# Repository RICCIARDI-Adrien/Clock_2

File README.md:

# Clock 2

Improved digital clock. First generation is [here](https://github.com/RICCIARDI-Adrien/Clock).  

New features :
* Improved temperature sensor.
* Humidity sensor.
* Pressure sensor.
* High accuracy temperature-compensated RTC.
* More compact, more industrial and more robust casing.
* A really simple interface made of 3 buttons to configure all clock settings (no more configuration through USB).

## Firmware

Microchip XC8 version 2.20 or above is required to build the firmware. Previous XC8 versions will work but the Celsius degree unit won't be displayed. This is due to a bug in XC8 escaped string characters parsing.

On a Linux system with XC8 installed and added to `PATH`, enter the following lines :
```
cd <repository directory>/Software
make
```

Resulting firmware file is `Firmware.hex`.

## Photo gallery

### PCB

### Display

### Casing

### Finished clock

Alarm stopping and display backlight button :

Power supply USB connector :

Bottom protection pads :

Internal view (backup battery not yet fitted) :

## Views

### Main

```
+--------------------+
|      11:16:23      |
|Jeudi    19/03/2020 |
| T:23°C  P:1112mBar |
| H:68%   A:OFF      |
+--------------------+
```

```
+--------------------+
|       0:37:11      |
|Dimanche 06/09/2020 |
| T:27°C  P:983mBar  |
| H:50%   A:ON(08:30)|
+--------------------+
```

'A' stands for a bell symbol representing the current alarm state (enabled or disabled).

### Statistics

Press `+` button to reach temperature view.  
Press `-` button to reach humidity view (these views can be accessed in reverse order).

```
+--------------------+
|---- TEMPERATURE ---|
|Minimum : 23°C      |
|Maximum : 15°C      |
|                    |
+--------------------+
```

Press `Set` or `-` button to return to main view.  
Press `+` button to go to pressure view.

```
+--------------------+
|----- PRESSION -----|
|Minimum : 980mbar   |
|Maximum : 1002mbar  |
|                    |
+--------------------+
```

Press `Set` to immediately return to main view.  
Press `-` button to return to temperature view.  
Press `+` button to go to humidity view.

```
+--------------------+
|----- HUMIDITE -----|
|Minimum : 57%       |
|Maximum : 59%       |
|                    |
+--------------------+
```

Press `Set` or `+` button to return to main view.  
Press `-` button to return to pression view.

### Settings

Press `Set` button to reach this view.

```
+--------------------+
|-> Régler alarme    |
|   Régler heure     |
|   Régler date      |
|       Retour       |
+--------------------+
```
Select a menu entry using `+` and `-` buttons, then press `Set` button.

### Set alarm

```
+--------------------+
|--- HEURE ALARME ---|
| Heure : 7          |
| + et - pour régler |
| SET pour continuer |
+--------------------+
```
Press `+` and `-` buttons to choose an hour, then press `Set` button to continue.

```
+--------------------+
|-- MINUTES ALARME --|
| Minutes : 30       |
| + et - pour régler |
| SET pour continuer |
+--------------------+
```
Press `+` and `-` buttons to choose minutes value, then press `Set` button to return to settings menu.

### Set time

```
+--------------------+
|--- REGLER HEURE ---|
| Heure : 11         |
| + et - pour régler |
| SET pour continuer |
+--------------------+
```
Press `+` and `-` buttons to choose an hour, then press `Set` button to continue.

```
+--------------------+
|-- REGLER MINUTES --|
| Minutes : 26       |
| + et - pour régler |
| SET pour continuer |
+--------------------+
```
Press `+` and `-` buttons to choose minutes value, then press `Set` button to continue.

```
+--------------------+
|- REGLER SECONDES --|
| Secondes : 47      |
| + et - pour régler |
| SET pour continuer |
+--------------------+
```
Press `+` and `-` buttons to choose seconds value, then press `Set` button to return to settings menu.

### Set date

```
+--------------------+
|--- REGLER JOUR ----|
| Jour : 14          |
| + et - pour régler |
| SET pour continuer |
+--------------------+
```
Press `+` and `-` buttons to choose a day, then press `Set` button to continue.

```
+--------------------+
|--- REGLER MOIS ----|
| Mois : 3           |
| + et - pour régler |
| SET pour continuer |
+--------------------+
```
Press `+` and `-` buttons to choose a month, then press `Set` button to continue.

```
+--------------------+
|--- REGLER ANNEE ---|
| Année : 2020       |
| + et - pour régler |
| SET pour continuer |
+--------------------+
```
Press `+` and `-` buttons to choose a year, then press `Set` button to return to settings menu.

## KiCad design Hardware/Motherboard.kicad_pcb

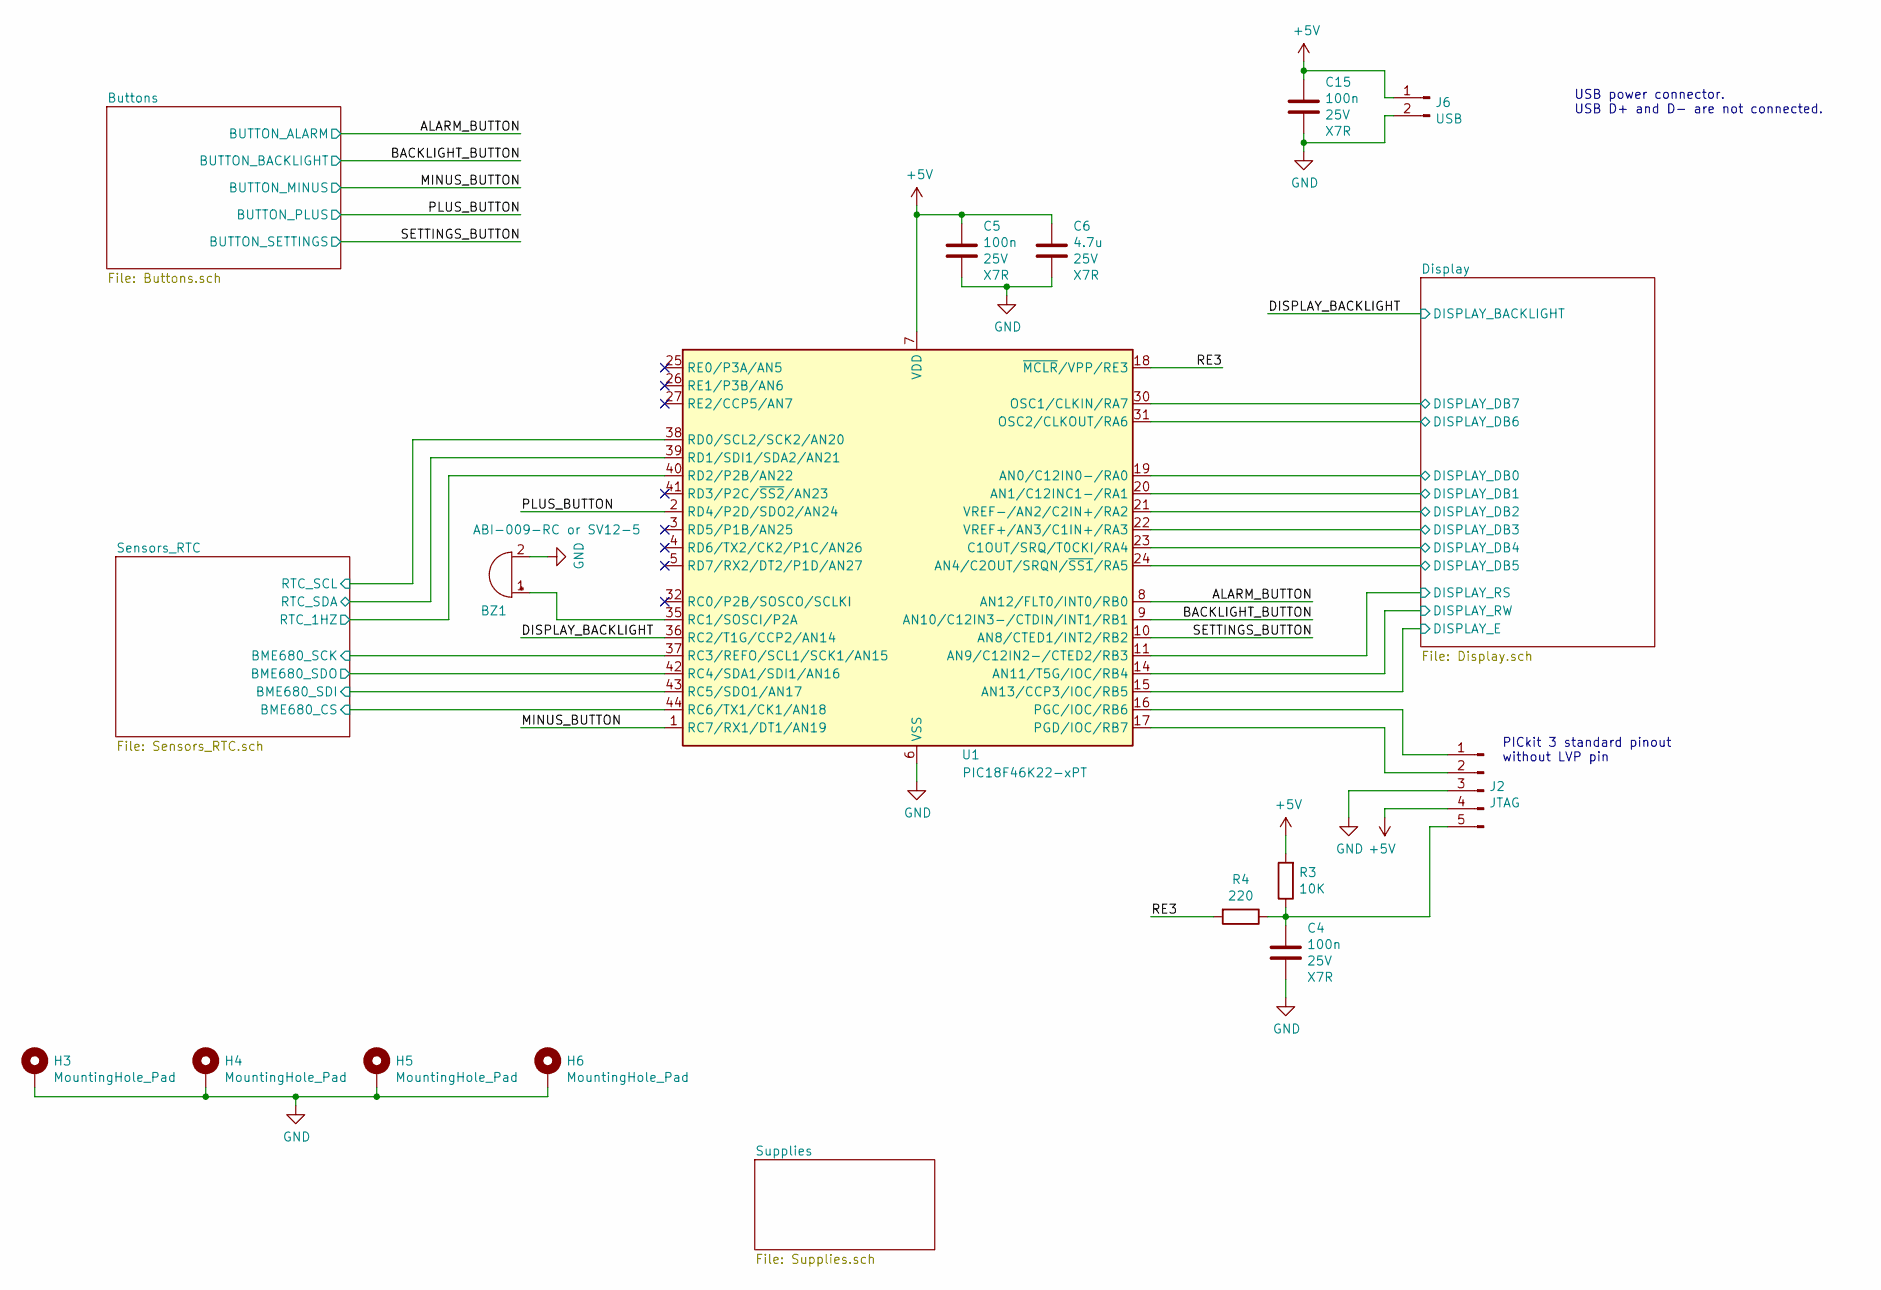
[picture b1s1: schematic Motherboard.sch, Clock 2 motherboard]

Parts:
BZ1: ABI-009-RC or SV12-5; MagneticBuzzer_ProSignal_ABI-009-RC
C4, C5, C15: 100n; C_1206_3216Metric_Pad1.42x1.75mm_HandSolder
C6: 4.7u; C_1206_3216Metric_Pad1.42x1.75mm_HandSolder
H3, H4, H5, H6: MountingHole_Pad; MountingHole_4.5mm_Pad
J2: JTAG; PinHeader_1x05_P2.54mm_Horizontal
J6: USB; PinHeader_1x02_P2.54mm_Vertical
R3: 10K; R_1206_3216Metric_Pad1.42x1.75mm_HandSolder
R4: 220; R_1206_3216Metric_Pad1.42x1.75mm_HandSolder
U1: PIC18F46K22-xPT; TQFP-44_10x10mm_P0.8mm

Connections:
+5V: C5.1, C6.1, C15.1, J2.4, J6.1, R3.2, U1.7 (VDD), U1.28 (VDD); also elsewhere on the board
/ALARM_BUTTON: U1.8 (AN12/FLT0/INT0/RB0); also elsewhere on the board
/BACKLIGHT_BUTTON: U1.9 (AN10/C12IN3-/CTDIN/INT1/RB1); also elsewhere on the board
/DISPLAY_BACKLIGHT: U1.36 (RC2/T1G/CCP2/AN14); also elsewhere on the board
/Display/DISPLAY_DB0: U1.19 (AN0/C12IN0-/RA0); also elsewhere on the board
/Display/DISPLAY_DB1: U1.20 (AN1/C12INC1-/RA1); also elsewhere on the board
/Display/DISPLAY_DB2: U1.21 (VREF-/AN2/C2IN+/RA2); also elsewhere on the board
/Display/DISPLAY_DB3: U1.22 (VREF+/AN3/C1IN+/RA3); also elsewhere on the board
/Display/DISPLAY_DB4: U1.23 (C1OUT/SRQ/T0CKI/RA4); also elsewhere on the board
/Display/DISPLAY_DB5: U1.24 (AN4/C2OUT/SRQN/~SS1~/RA5); also elsewhere on the board
/Display/DISPLAY_DB6: U1.31 (OSC2/CLKOUT/RA6); also elsewhere on the board
/Display/DISPLAY_DB7: U1.30 (OSC1/CLKIN/RA7); also elsewhere on the board
/Display/DISPLAY_E: U1.15 (AN13/CCP3/IOC/RB5); also elsewhere on the board
/Display/DISPLAY_RS: U1.11 (AN9/C12IN2-/CTED2/RB3); also elsewhere on the board
/Display/DISPLAY_RW: U1.14 (AN11/T5G/IOC/RB4); also elsewhere on the board
/MINUS_BUTTON: U1.1 (RC7/RX1/DT1/AN19); also elsewhere on the board
/PLUS_BUTTON: U1.2 (RD4/P2D/SDO2/AN24); also elsewhere on the board
/RE3: R4.2, U1.18 (~MCLR~/VPP/RE3)
/SETTINGS_BUTTON: U1.10 (AN8/CTED1/INT2/RB2); also elsewhere on the board
/Sensors_RTC/BME680_CS: U1.44 (RC6/TX1/CK1/AN18); also elsewhere on the board
/Sensors_RTC/BME680_SCK: U1.37 (RC3/REFO/SCL1/SCK1/AN15); also elsewhere on the board
/Sensors_RTC/BME680_SDI: U1.43 (RC5/SDO1/AN17); also elsewhere on the board
/Sensors_RTC/BME680_SDO: U1.42 (RC4/SDA1/SDI1/AN16); also elsewhere on the board
/Sensors_RTC/RTC_1HZ: U1.40 (RD2/P2B/AN22); also elsewhere on the board
/Sensors_RTC/RTC_SCL: U1.38 (RD0/SCL2/SCK2/AN20); also elsewhere on the board
/Sensors_RTC/RTC_SDA: U1.39 (RD1/SDI1/SDA2/AN21); also elsewhere on the board
GND: BZ1.2 (+), C4.2, C5.2, C6.2, C15.2, H3.1, H4.1, H5.1, H6.1, J2.3, J6.2, U1.6 (VSS), U1.29 (VSS); also elsewhere on the board
unnamed: BZ1.1 (-), U1.35 (RC1/SOSCI/P2A)
unnamed: C4.1, J2.5, R3.1, R4.1
unnamed: J2.1, U1.16 (PGC/IOC/RB6)
unnamed: J2.2, U1.17 (PGD/IOC/RB7)

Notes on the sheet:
PICkit 3 standard pinout without LVP pin
USB power connector. USB D+ and D- are not connected.

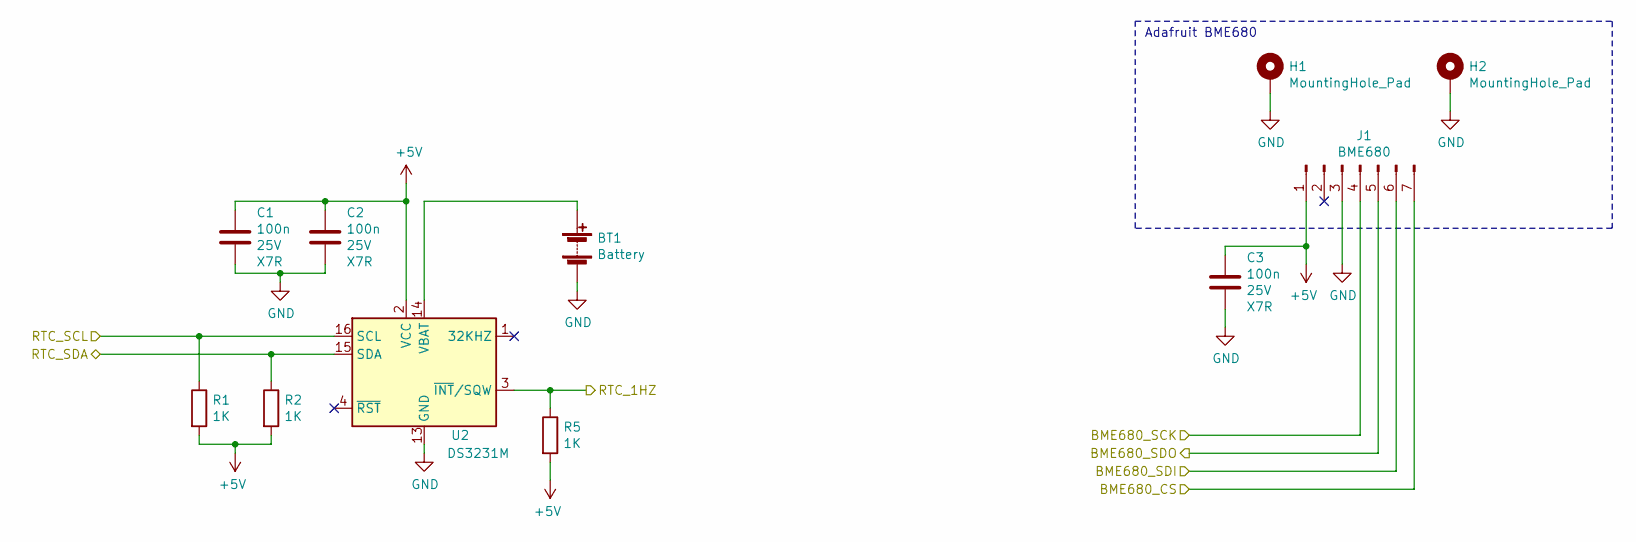
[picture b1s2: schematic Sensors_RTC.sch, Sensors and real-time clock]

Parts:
BT1: Battery; BatteryHolder_Keystone_103_1x20mm
C1, C2, C3: 100n; C_1206_3216Metric_Pad1.42x1.75mm_HandSolder
H1, H2: MountingHole_Pad; MountingHole_2.7mm_Pad
J1: BME680; PinHeader_1x07_P2.54mm_Vertical
R1, R2, R5: 1K; R_1206_3216Metric_Pad1.42x1.75mm_HandSolder
U2: DS3231M; SOIC-16W_7.5x10.3mm_P1.27mm

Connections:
+5V: C1.2, C2.2, C3.2, J1.1, R1.2, R2.2, R5.2, U2.2 (VCC); also elsewhere on the board
/Sensors_RTC/BME680_CS: J1.7; also elsewhere on the board
/Sensors_RTC/BME680_SCK: J1.4; also elsewhere on the board
/Sensors_RTC/BME680_SDI: J1.6; also elsewhere on the board
/Sensors_RTC/BME680_SDO: J1.5; also elsewhere on the board
/Sensors_RTC/RTC_1HZ: R5.1, U2.3 (~INT~/SQW); also elsewhere on the board
/Sensors_RTC/RTC_SCL: R1.1, U2.16 (SCL); also elsewhere on the board
/Sensors_RTC/RTC_SDA: R2.1, U2.15 (SDA); also elsewhere on the board
GND: BT1.2 (-), C1.1, C2.1, C3.1, H1.1, H2.1, J1.3, U2.5 (GND), U2.6 (GND), U2.7 (GND), U2.8 (GND), U2.9 (GND), U2.10 (GND), U2.11 (GND), U2.12 (GND), U2.13 (GND); also elsewhere on the board
unnamed: BT1.1 (+), U2.14 (VBAT)

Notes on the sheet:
Adafruit BME680

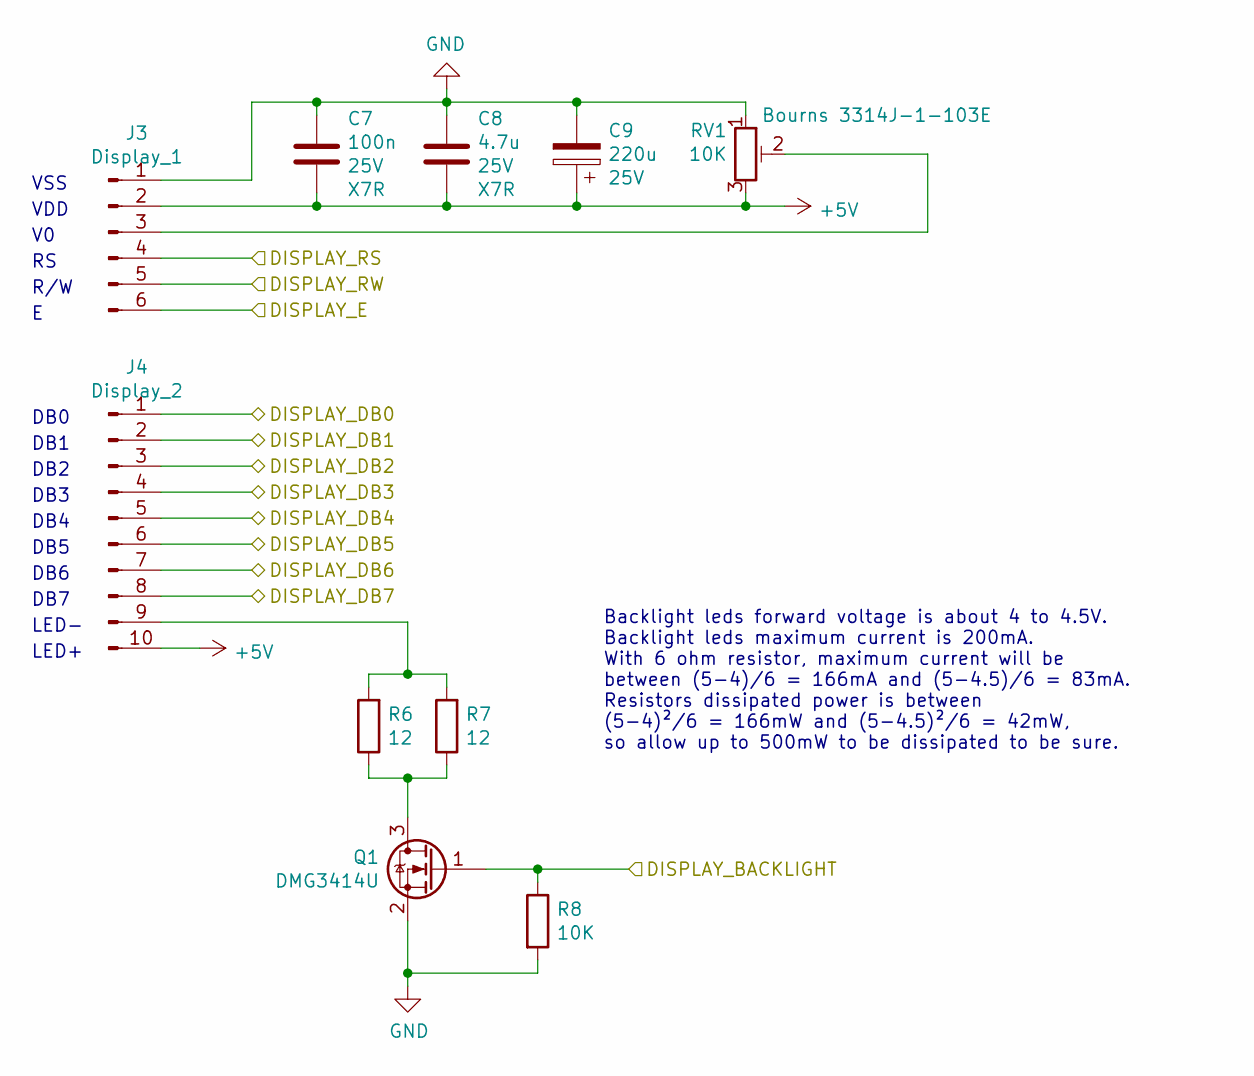
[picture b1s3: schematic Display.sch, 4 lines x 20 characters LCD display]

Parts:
C7: 100n; C_1206_3216Metric_Pad1.42x1.75mm_HandSolder
C8: 4.7u; C_1206_3216Metric_Pad1.42x1.75mm_HandSolder
C9: 220u; CP_Elec_8x10.5
J3: Display_1; PinHeader_1x06_P2.54mm_Vertical
J4: Display_2; PinHeader_1x10_P2.54mm_Vertical
Q1: DMG3414U; SOT-23
R6, R7: 12; R_1206_3216Metric_Pad1.42x1.75mm_HandSolder
R8: 10K; R_1206_3216Metric_Pad1.42x1.75mm_HandSolder
RV1: 10K; Potentiometer_Bourns_3314J_Vertical

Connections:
+5V: C7.2, C8.2, C9.1, J3.2, J4.10, RV1.3; also elsewhere on the board
/DISPLAY_BACKLIGHT: Q1.1 (G), R8.1; also elsewhere on the board
/Display/DISPLAY_DB0: J4.1; also elsewhere on the board
/Display/DISPLAY_DB1: J4.2; also elsewhere on the board
/Display/DISPLAY_DB2: J4.3; also elsewhere on the board
/Display/DISPLAY_DB3: J4.4; also elsewhere on the board
/Display/DISPLAY_DB4: J4.5; also elsewhere on the board
/Display/DISPLAY_DB5: J4.6; also elsewhere on the board
/Display/DISPLAY_DB6: J4.7; also elsewhere on the board
/Display/DISPLAY_DB7: J4.8; also elsewhere on the board
/Display/DISPLAY_E: J3.6; also elsewhere on the board
/Display/DISPLAY_RS: J3.4; also elsewhere on the board
/Display/DISPLAY_RW: J3.5; also elsewhere on the board
GND: C7.1, C8.1, C9.2, J3.1, Q1.2 (S), R8.2, RV1.1; also elsewhere on the board
unnamed: J3.3, RV1.2
unnamed: J4.9, R6.2, R7.2
unnamed: Q1.3 (D), R6.1, R7.1

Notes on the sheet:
DB0
DB1
DB2
DB3
DB4
DB5
DB6
DB7
VSS
VDD
R/W
LED-
LED+
Backlight leds forward voltage is about 4 to 4.5V. Backlight leds maximum current is 200mA. With 6 ohm resistor, maximum current will be between (5-4)/6 = 166mA and (5-4.5)/6 = 83mA. Resistors dissipated power is between (5-4)²/6 = 166mW and (5-4.5)²/6 = 42mW, so allow up to 500mW to be dissipated 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

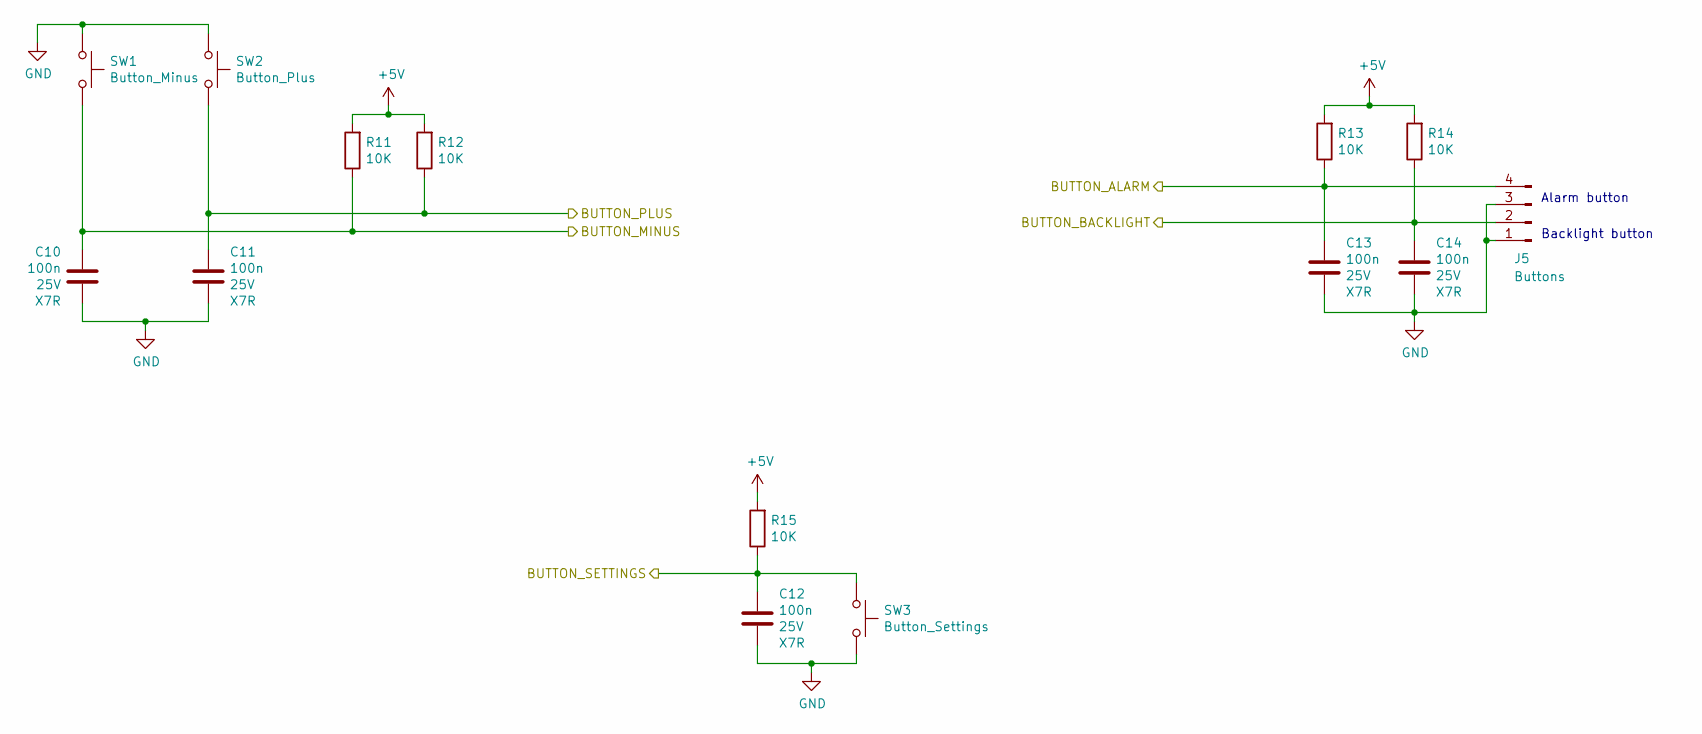
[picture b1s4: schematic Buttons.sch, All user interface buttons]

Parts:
C10, C11, C12, C13, C14: 100n; C_1206_3216Metric_Pad1.42x1.75mm_HandSolder
J5: Buttons; PinHeader_1x04_P2.54mm_Vertical
R11, R12, R13, R14, R15: 10K; R_1206_3216Metric_Pad1.42x1.75mm_HandSolder
SW1: Button_Minus; SW_Tactile_SKHH_Angled
SW2: Button_Plus; SW_Tactile_SKHH_Angled
SW3: Button_Settings; SW_Tactile_SKHH_Angled

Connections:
+5V: R11.2, R12.2, R13.2, R14.2, R15.2; also elsewhere on the board
/ALARM_BUTTON: C13.2, J5.4, R13.1; also elsewhere on the board
/BACKLIGHT_BUTTON: C14.2, J5.2, R14.1; also elsewhere on the board
/MINUS_BUTTON: C10.2, R11.1, SW1.2; also elsewhere on the board
/PLUS_BUTTON: C11.2, R12.1, SW2.2; also elsewhere on the board
/SETTINGS_BUTTON: C12.2, R15.1, SW3.2; also elsewhere on the board
GND: C10.1, C11.1, C12.1, C13.1, C14.1, J5.1, J5.3, SW1.1, SW2.1, SW3.1; also elsewhere on the board

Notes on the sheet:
Alarm button
Backlight button

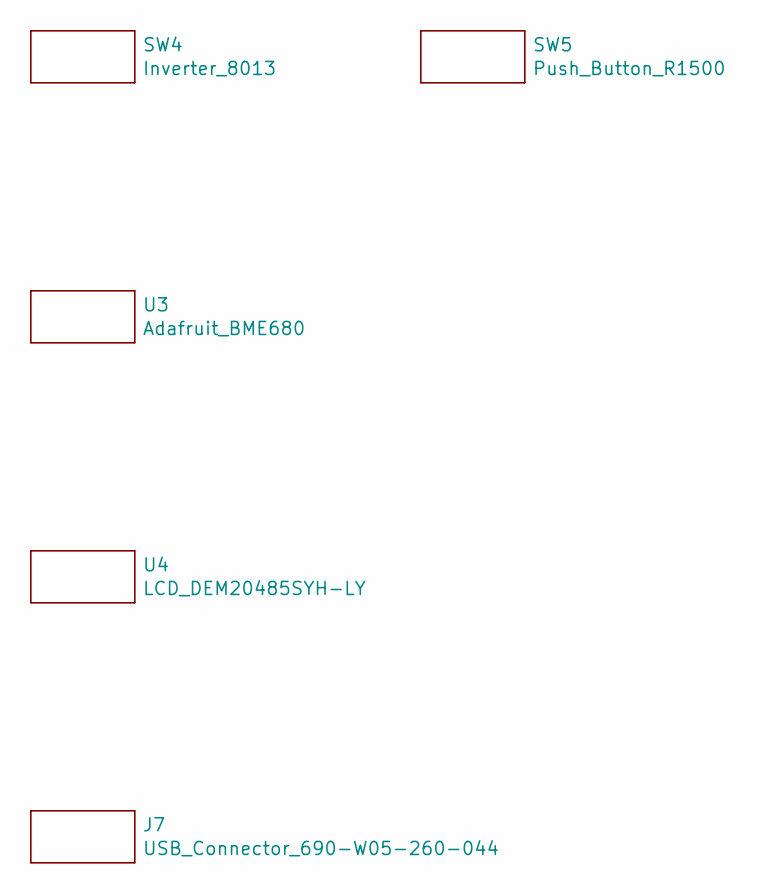
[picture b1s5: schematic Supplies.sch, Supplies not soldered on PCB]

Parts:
J7: USB_Connector_690-W05-260-044; Supply_Part
SW4: Inverter_8013; Supply_Part
SW5: Push_Button_R1500; Supply_Part
U3: Adafruit_BME680; Supply_Part
U4: LCD_DEM20485SYH-LY; Supply_Part

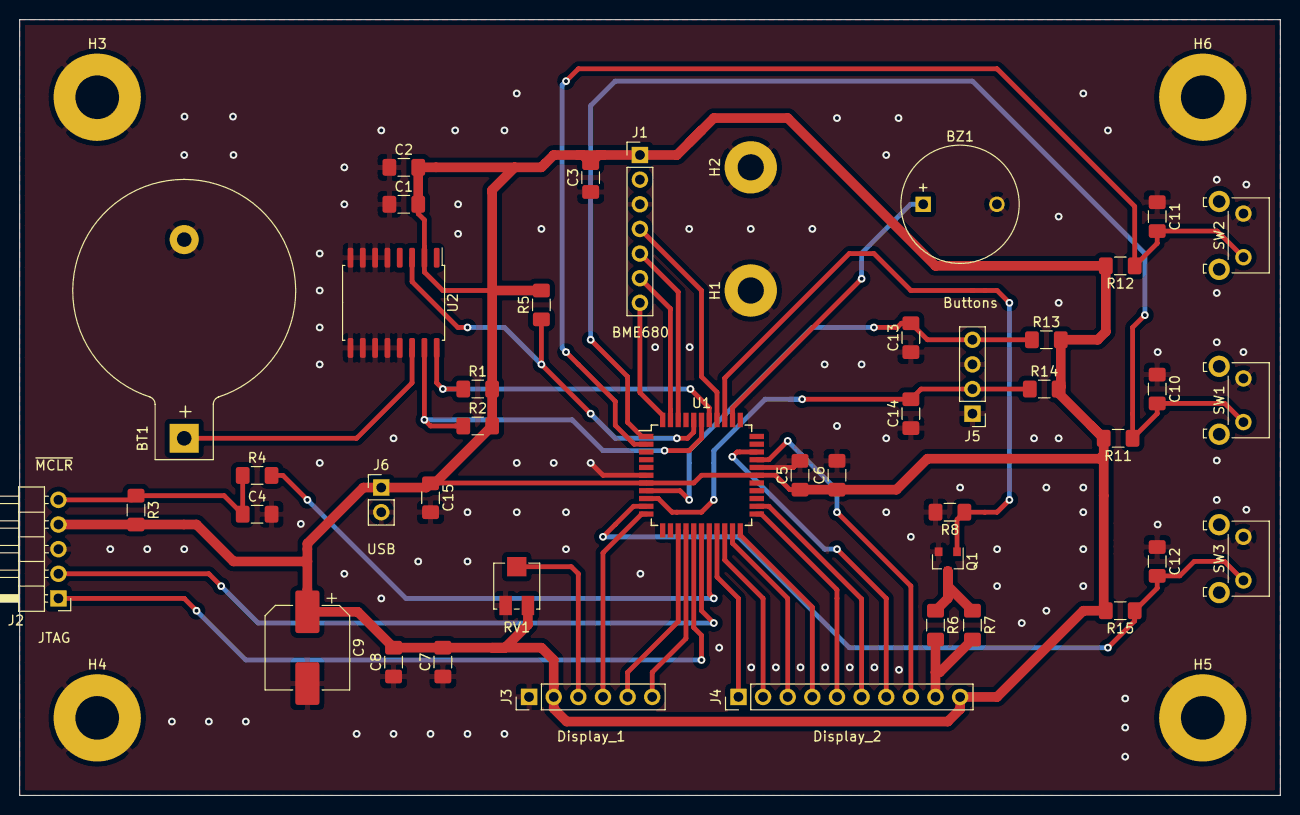
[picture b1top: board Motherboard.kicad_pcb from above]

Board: 2 copper layers, 130.0 x 80.0 mm, 54 parts (0 on the bottom side), 35 nets.

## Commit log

2020-03-24 Initial commit. Added .gitignore file.
2020-03-24 [Hardware] Started schematic. Added BME680 sensor and RTC.
2020-03-24 Added README.md.
2020-03-24 [Hardware] Added RTC battery and Adafruit BME680 board.
2020-03-24 [Hardware] Replaced PIC18F26K22 microcontroller by PIC18F46K22 to have more pins.
2020-03-24 [Hardware] Added display support.
2020-03-24 [Resources] Added display, display controller, microcontroller and RTC datasheets.
2020-03-25 [Hardware] Added buttons.
2020-03-25 [Hardware] Added simpler buttons debouncing and also added debouncing to buttons that trigger an interrupt.
2020-03-25 [Hardware] Added all schematic parts (but not all external parts, like display or female connectors).
2020-03-25 [Hardware] Started PCB routing. Components are placed, BME680 board mounting holes are in position, some nets are connected.
2020-03-26 [Hardware] Moved buttons to another schematic sheet and fully routed PCB.
2020-03-26 [Hardware] Used a custom empty footprint for Adafruit module part. This way, part is visible in schematic and bill of materials, but it is not part of the PCB.
2020-03-26 [Hardware] Added display part in both schematic and PCB.
2020-03-26 [Hardware] Swapped programming connector to have it in the right order.
2020-03-26 [Hardware] Displayed project date on PCB.
2020-03-26 [Hardware] Added alarm and backlight buttons parts to both schematic and PCB.
2020-03-26 [Hardware] Removed KiCad cache file from repository.
2020-03-27 [Hardware] Added USB connector supply part to both schematic and PCB.
2020-03-27 [Hardware] Renamed LCD display symbol for more coherency.
2020-04-18 [Hardware] Slightly decreased PCB width and adjusted it to millimeters.
2020-04-18 Added more KiCad temporary files to .gitignore.
2020-04-18 [Hardware] Slightly decreased PCB height and adjusted it to millimeters.
2020-04-18 [Hardware] Moved PCB mounting holes to fit new board dimensions.
2020-04-18 [Hardware] Added PCB switches 3D model.
2020-04-18 [Hardware] Filled some empty bottom layer areas with ground plane.
2020-04-19 [Hardware] Displayed connectors usage and button names on PCB.
2020-04-21 [Hardware] Replaced each supply part by a generic one to avoid creating a new symbol for every supply part.
2020-04-24 [Software] Started firmware implementation. Configured microcontroller fuses and added a basic test that blinks the display background.
2020-04-24 [Software] Started display driver. Display initialization works and a test text is displayed.
2020-04-24 [Software] Added DisplayWriteCharacter() and DisplaySetCursorLocation() functions, along with an unit test.
2020-04-24 [Software] Added RTC initialization and unit test reading chip 'seconds' register.
2020-04-24 [Software] Enabled 1Hz square-wave generation by RTC.
2020-04-25 [Software] Added a function to directly write numbers to the display and improved display cursor location handling.
2020-04-25 [Software] Started BME680 sensor driver. It is able to read the chip ID.
2020-04-25 [Software] Added time retrieval from RTC registers and displayed it on screen.
2020-04-26 [Software] Added date retrieval from RTC registers and displayed it on screen.
2020-04-26 [Software] Added configuration buttons support and a test configuration menu view.
2020-04-26 [Software] Used BME680 library provided by sensor manufacturer. Switched C standard to C99 to be able to build this library.
2020-04-26 [Software] Retrieved pressure and humidity from BME680 sensor and displayed them.
2020-04-26 [Software] Disabled BME680 gas sensor for now as air quality computations seem hard to find.
2020-04-27 [Software] Added 'e acute' special display character.
2020-04-27 [Software] Added buttons support to configuration menu view.
2020-04-27 [Software] Moved menu buttons related functions to a dedicated module.
2020-04-28 [Software] Added time configuration view. Configured time is not written to RTC yet.
2020-04-28 [Software] Added RTC time setting.
2020-04-28 Updated views in README.md.
2020-04-28 [Software] Added date configuration view.
2020-04-28 [Software] Avoided out-of-range values to be displayed by number selection view.
2020-04-28 [Software] Added automatic day of week determination when setting RTC date.
2020-04-28 [Software] Inverted 'plus' and 'minus' buttons to make them match PCB marking.
2020-04-28 [Software] Added display backlight functions.
2020-04-28 [Software] Added backlight button support.
2020-04-29 [Software] Added ring support.
2020-04-29 [Software] Renamed 'Menu_Button' module in 'Buttons', so it can also handle alarm and backlight buttons.
2020-04-29 [Software] Moved backlight button code to 'Buttons' module.
2020-04-29 [Hardware] Swapped 'plus' and 'minus' buttons in both schematic and PCB to match final buttons position.
2020-04-29 [Software] Added alarm values writing to and reading from RTC.
2020-04-29 [Software] Added alarm configuration views.
2020-04-29 [Software] Added alarm support and slightly increased ring melody duration.
2020-04-29 [Software] Inverted 'plus' and 'minus' buttons behavior in configuration menu view to make the menu feel more intuitive.
2020-04-29 [Software] Renamed DISPLAY_LOCATION_LINE_x constants as DISPLAY_CURSOR_LOCATION_LINE_x for more coherency.
2020-04-29 [Resources] Added PCB and display pictures.
2020-04-29 [Software] Displayed alarm state on main view.
2020-04-29 Displayed alarm state in README.md main view.
2020-05-01 [Resources] Added mini USB connector datasheet.
2020-05-01 [Resources] Gathered datasheets in a dedicated directory.
2020-05-02 [Software] Set default date, time and alarm when RTC data are corrupted to avoid displaying impossible values.
2020-05-04 [Casing] Started casing design. Added bottom face.
2020-05-08 [Casing] Added remaining faces. Construction lines are still present.
2020-05-08 [Casing] Removed construction lines.
2020-05-15 [Resources] Added casing steel plates picture.
2020-05-28 [Software] Added views to display minimum and maximum values for temperature, pression and humidity.
2020-05-28 [Software] Discarded Celsius degree character hack now that XC8 2.20 is able to correctly parse escaped characters.
2020-05-28 Added firmware build instructions to README.md.
2020-06-06 [Software] Increased BME680 humidity oversampling to get more precise measures.
2020-06-07 [Software] Used an enum for measure views IDs in order to make code easier to read.
2020-06-07 [Software] Used an enum for setting menu IDs in order to make code easier to read.
2020-06-07 Added finished clock pictures to README.md.
2020-06-14 Swapped 'Views' and 'Photo gallery' sections in README.md.
2020-06-14 Added statistics views to README.md.
2020-06-17 [Software] Fixed a bug : an alarm hour greater than 19 could not be set.
2020-06-17 [Software] Improved ring melody.
2020-06-17 [Software] Added display backlight lighting when alarm starts ringing.
2020-09-05 [Software] Added alarm time displaying to default view when alarm is enabled.
2020-09-05 Added enabled alarm view to README.md.
